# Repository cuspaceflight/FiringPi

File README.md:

# FiringPi

This project is designed to be run on a Raspberry Pi connected to various peripherals, to act as both fire controller
and datalogger for CUSF's White Dwarf hot and cold test fires. The utility files only run on linux, but you should be
able to work out equivalent commands for windows if you need to (if you do this please do put them in a .bat file and
pull request.).

## Requirements

To build on your local machine, you will need a native cross-compiler such
as [gcc/g++](https://www.gnu.org/software/gcc/) (You can change the compiler by editing the variable `$(GXX)` in a local
copy of the makfile and specifying `-f <local.makefile>` in the make command. The project
uses [ncurses](https://invisible-island.net/ncurses/announce.html) for its TUI, which works over standard ssh tty. You
will therefore need to make sure you have at least `libncurses5-dev` and `libncursesw5-dev` installed. When running on
the Raspberry Pi, [WiringPi](http://wiringpi.com/) is used for gpio access, which will need to be installed on your
local machine to compile if you wish to do so. The raspberry Pi also uses [tmux](https://linuxhandbook.com/tmux/) to
manage disconnects safely (the system leaving all of the valves open after an unhandled disconnect would not be good),
so if you use the script [/pi](/pi), then you will also require this. All of these are already installed on the flight
computer.

## Building and running

Clone the repo, then assert the directory is set up correctly with `make clean`. For a local build, use the makefile:

```console
make && ./main
```

To build on the Pi, you need to have ssh access, and make sure you have updated its IP address in either [/pi](/pi).
This file contains a script to upload source code directly to the Pi (with scp, no need for a git sync) and execute it
over ssh, forcing interactive terminal allocation, then building the project on the pi and executing it in a detatched
tmux session. You can also just run the executable on the pi in tmux without building with `./pi -r` or conversely to
build without running `./pi -b`

## Using the Program {curly brackets mean TODO}

Once you have launched the TUI successfully, you must launch the system into SAFE mode by pressing s[afe]. The system
may be armed by pressing <CTRL-A>, then {once you are satisfied that the system has booted correctly,} IGNITION mode may
be entered by pressing <SPACE>. The computer will then enter IGNITION, followed by FIRING and SHUTDOWN {as it runs the
preconfigured fire sequence}. An ABORT may be triggered by pressing <BACKSPACE> {or automatically by the system
detecting unsafe parameters}. ABORT mode can only be exitied by the computer, for safety reasons {currently press
e[rror] to debug exit}. SHUTDOWN exits to SAFE, and ABORT exits to ERROR, from which SAFE mode can be entered by
pressing s[afe]. To quit the program, the system must first be in the OFF state, entered by pressing o[ff] from SAFE
mode, only then it will exit when q[uit] is pressed.

## Project Structure

```markdown
cft-controller
├── build
│   ├── Display.o
│   ├── main.o
│   └── State.o
├── include
│   ├── Display.hpp
│   └── State.hpp
├── main
├── Makefile
├── pi
├── README.md
├── src
│   ├── Display.cpp
│   ├── main.cpp
│   └── State.cpp
└── TODO.md
```

## Useful Stuff

[ncurses HOWTO](https://tldp.org/HOWTO/NCURSES-Programming-HOWTO/)

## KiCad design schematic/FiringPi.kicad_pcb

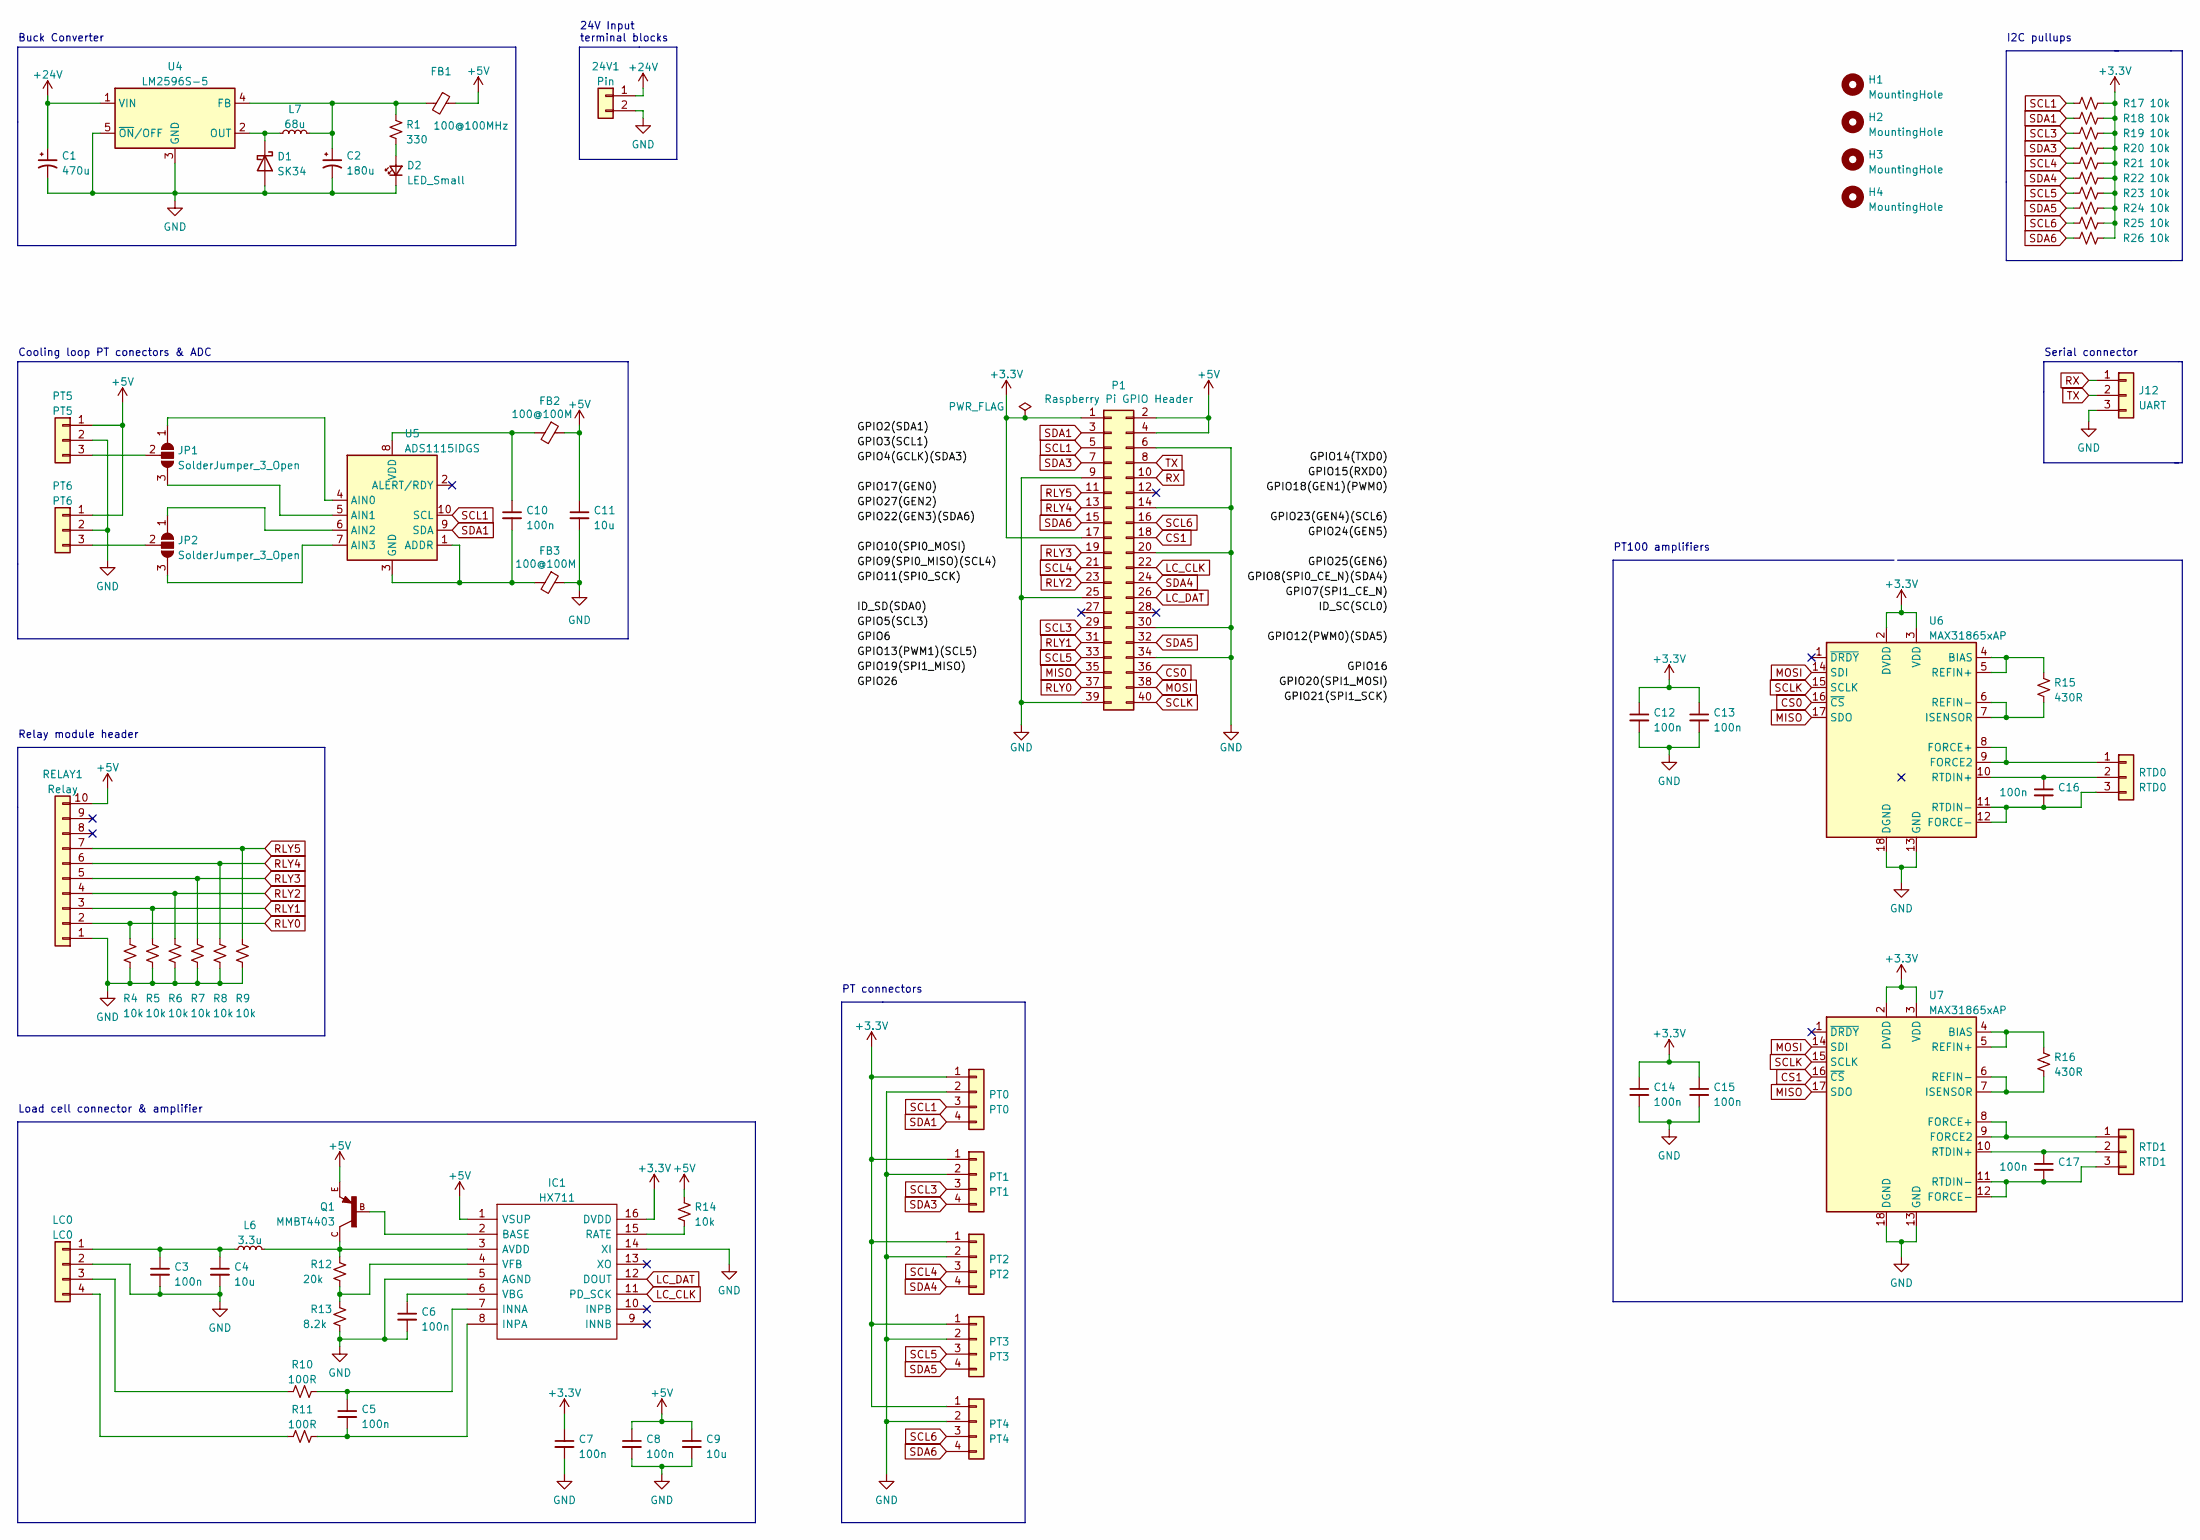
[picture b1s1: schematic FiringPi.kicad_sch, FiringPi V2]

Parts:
24V1: Pin; JST_XH_B2B-XH-A_1x02_P2.50mm_Vertical
C1: 470u; CP_Radial_D12.5mm_P5.00mm
C2: 180u; CP_Radial_D8.0mm_P3.50mm
C3, C5, C6, C7, C8, C10, C12, C13, C14, C15, C16, C17: 100n; C_0603_1608Metric
C4, C9, C11: 10u; C_0603_1608Metric
D1: SK34; D_SMC
D2: LED_Small; LED_0805_2012Metric
FB1: 100@100MHz; L_0805_2012Metric
FB2, FB3: 100@100M; L_0805_2012Metric
H1, H2, H3, H4: MountingHole; MountingHole_2.7mm_M2.5
IC1: HX711; SOIC127P600X160-16N; Manufacturer_Part_Number HX711
J12: UART; JST_XH_B3B-XH-A_1x03_P2.50mm_Vertical
JP1, JP2: SolderJumper_3_Open; SolderJumper-3_P1.3mm_Open_RoundedPad1.0x1.5mm
L6: 3.3u; L_0603_1608Metric
L7: 68u; PE-54038SNL
LC0: LC0; JST_XH_B4B-XH-A_1x04_P2.50mm_Vertical
P1: Raspberry Pi GPIO Header; PinSocket_2x20_P2.54mm_Vertical
PT0: PT0; JST_XH_B4B-XH-A_1x04_P2.50mm_Vertical
PT1: PT1; JST_XH_B4B-XH-A_1x04_P2.50mm_Vertical
PT2: PT2; JST_XH_B4B-XH-A_1x04_P2.50mm_Vertical
PT3: PT3; JST_XH_B4B-XH-A_1x04_P2.50mm_Vertical
PT4: PT4; JST_XH_B4B-XH-A_1x04_P2.50mm_Vertical
PT5: PT5; JST_XH_B3B-XH-A_1x03_P2.50mm_Vertical
PT6: PT6; JST_XH_B3B-XH-A_1x03_P2.50mm_Vertical
Q1: MMBT4403; SOT23-BEC
R1: 330; R_0603_1608Metric
R4, R5, R6, R7, R8, R9, R14, R17, R18, R19, R20, R21, R22, R23, R24, R25, R26: 10k; R_0603_1608Metric
R10, R11: 100R; R_0603_1608Metric
R12: 20k; R_0603_1608Metric
R13: 8.2k; R_0603_1608Metric
R15, R16: 430R; R_0603_1608Metric
RELAY1: Relay; PinHeader_1x10_P2.54mm_Vertical
RTD0: RTD0; JST_XH_B3B-XH-A_1x03_P2.50mm_Vertical
RTD1: RTD1; JST_XH_B3B-XH-A_1x03_P2.50mm_Vertical
U4: LM2596S-5; TO-263-5_TabPin3
U5: ADS1115IDGS; TSSOP-10_3x3mm_P0.5mm
U6, U7: MAX31865xAP; SSOP-20_5.3x7.2mm_P0.65mm

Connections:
+3.3V: C7.1, C12.1, C13.1, C14.1, C15.1, IC1.16 (DVDD), P1.1, P1.17, PT0.1, PT1.1, PT2.1, PT3.1, PT4.1, R17.1, R18.1, R19.1, R20.1, R21.1, R22.1, R23.1, R24.1, R25.1, R26.1, U6.2 (DVDD), U6.3 (VDD), U7.2 (DVDD), U7.3 (VDD)
+5V: C8.1, C9.1, C11.1, FB1.1, FB2.1, IC1.1 (VSUP), P1.2, P1.4, PT5.1, PT6.1, Q1.E, R14.1, RELAY1.10
+24V: 24V1.1, C1.1, U4.1 (VIN)
CS0: P1.36, U6.16 (~CS)
CS1: P1.18, U7.16 (~CS)
GND: 24V1.2, C1.2, C2.2, C3.2, C4.2, C6.2, C7.2, C8.2, C9.2, C11.2, C12.2, C13.2, C14.2, C15.2, D1.2 (A), D2.1 (K), FB3.1, IC1.5 (AGND), IC1.14 (XI), J12.3, LC0.2, P1.6, P1.9, P1.14, P1.20, P1.25, P1.30, P1.34, P1.39, PT0.2, PT1.2, PT2.2, PT3.2, PT4.2, PT5.2, PT6.2, R4.2, R5.2, R6.2, R7.2, R8.2, R9.2, R13.2, RELAY1.1, U4.3 (GND), U4.5 (~ON/OFF), U6.13 (GND), U6.18 (DGND), U6.19 (GND), U7.13 (GND), U7.18 (DGND), U7.19 (GND)
LC_CLK: IC1.11 (PD_SCK), P1.22
LC_DAT: IC1.12 (DOUT), P1.26
MISO: P1.35, U6.17 (SDO), U7.17 (SDO)
MOSI: P1.38, U6.14 (SDI), U7.14 (SDI)
unnamed: C2.1, FB1.2, L7.2, R1.1, U4.4 (FB)
unnamed: C3.1, C4.1, L6.1, LC0.1
unnamed: C5.1, IC1.7 (INNA), R10.1
unnamed: C5.2, IC1.8 (INPA), R11.1
unnamed: C6.1, IC1.6 (VBG)
unnamed: C10.1, FB2.2, U5.8 (VDD)
unnamed: C10.2, FB3.2, U5.1 (ADDR), U5.3 (GND)
unnamed: C16.1, RTD0.2, U6.10 (RTDIN+)
unnamed: C16.2, RTD0.3, U6.11 (RTDIN-), U6.12 (FORCE-)
unnamed: C17.1, RTD1.2, U7.10 (RTDIN+)
unnamed: C17.2, RTD1.3, U7.11 (RTDIN-), U7.12 (FORCE-)
unnamed: D1.1 (K), L7.1, U4.2 (OUT)
unnamed: D2.2 (A), R1.2
unnamed: IC1.2 (BASE), Q1.B
unnamed: IC1.3 (AVDD), L6.2, Q1.C, R12.1
unnamed: IC1.4 (VFB), R12.2, R13.1
unnamed: IC1.15 (RATE), R14.2
unnamed: JP1.1 (A), U5.4 (AIN0)
unnamed: JP1.2 (C), PT5.3
unnamed: JP1.3 (B), U5.5 (AIN1)
unnamed: JP2.1 (A), U5.6 (AIN2)
unnamed: JP2.2 (C), PT6.3
unnamed: JP2.3 (B), U5.7 (AIN3)
unnamed: LC0.3, R10.2
unnamed: LC0.4, R11.2
unnamed: R15.1, U6.4 (BIAS), U6.5 (REFIN+)
unnamed: R15.2, U6.6 (REFIN-), U6.7 (ISENSOR)
unnamed: R16.1, U7.4 (BIAS), U7.5 (REFIN+)
unnamed: R16.2, U7.6 (REFIN-), U7.7 (ISENSOR)
unnamed: RTD0.1, U6.8 (FORCE+), U6.9 (FORCE2)
unnamed: RTD1.1, U7.8 (FORCE+), U7.9 (FORCE2)
RLY0: P1.37, R4.1, RELAY1.2
RLY1: P1.31, R5.1, RELAY1.3
RLY2: P1.23, R6.1, RELAY1.4
RLY3: P1.19, R7.1, RELAY1.5
RLY4: P1.13, R8.1, RELAY1.6
RLY5: P1.11, R9.1, RELAY1.7
RX: J12.1, P1.10
SCL1: P1.5, PT0.3, R17.2, U5.10 (SCL)
SCL3: P1.29, PT1.3, R19.2
SCL4: P1.21, PT2.3, R21.2
SCL5: P1.33, PT3.3, R23.2
SCL6: P1.16, PT4.3, R25.2
SCLK: P1.40, U6.15 (SCLK), U7.15 (SCLK)
SDA1: P1.3, PT0.4, R18.2, U5.9 (SDA)
SDA3: P1.7, PT1.4, R20.2
SDA4: P1.24, PT2.4, R22.2
SDA5: P1.32, PT3.4, R24.2
SDA6: P1.15, PT4.4, R26.2
TX: J12.2, P1.8

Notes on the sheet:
Serial connector
PT100 amplifiers
PT connectors
I2C pullups
Load cell connector & amplifier
24V Input terminal blocks
Buck Converter
Relay module header
Cooling loop PT conectors & ADC

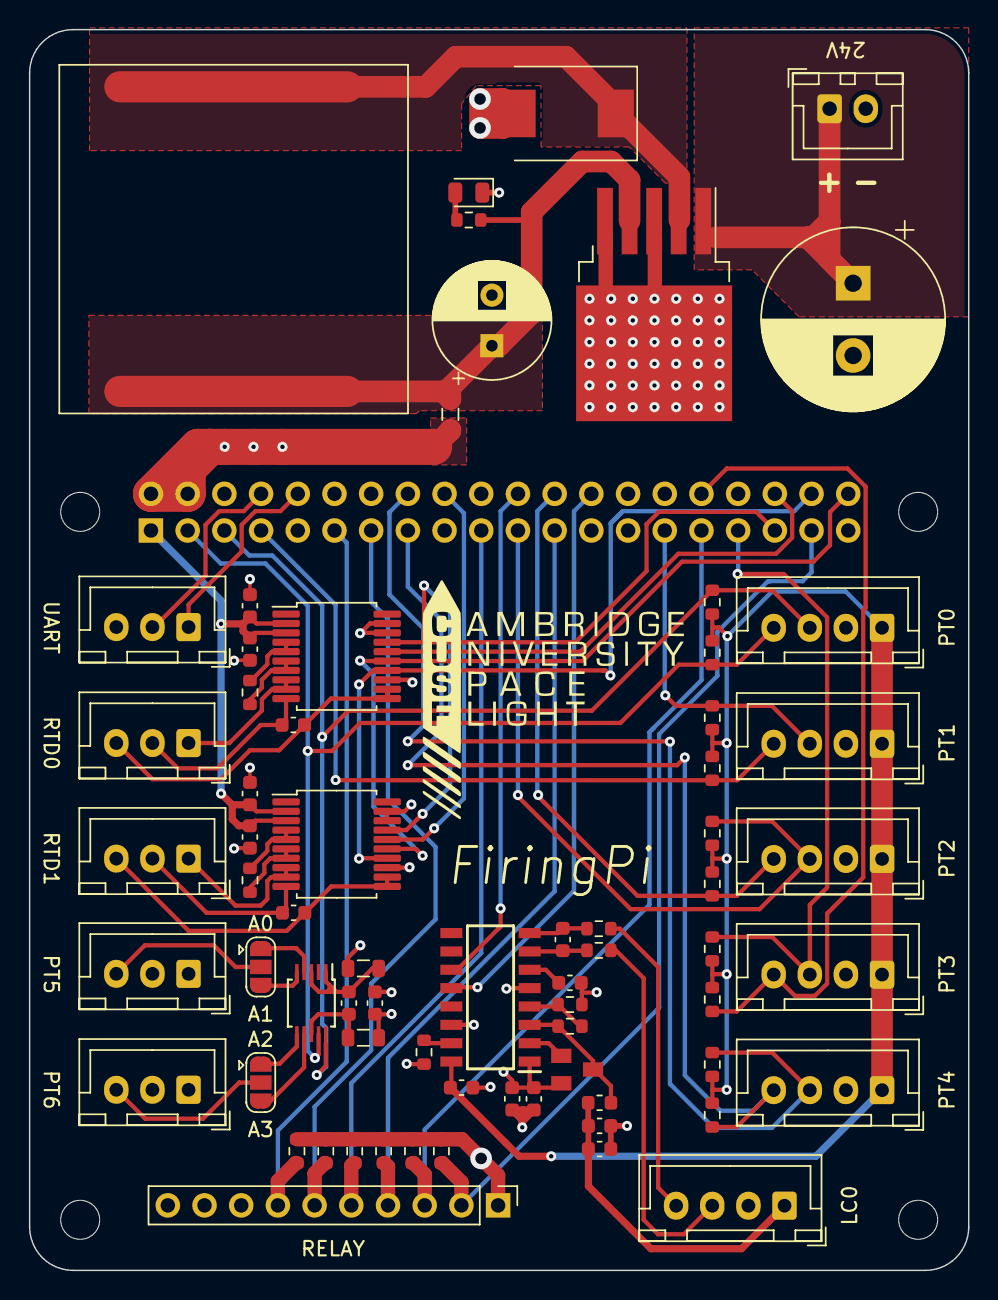
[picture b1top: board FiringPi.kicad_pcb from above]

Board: 4 copper layers, 65.0 x 85.9 mm, 74 parts (1 on the bottom side), 60 nets.

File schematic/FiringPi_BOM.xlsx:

FiringPi
Id | Designator | Package | Quantity | Designation | Part No | Suppplier | Supplier part no | Order quantity | Unit cost | Total cost
5 | J12 | JST_XH_B3B-XH-A_1x03_P2.50mm_Vertical | 5 | UART, PT5, PT6, RTD, RTD1 |  |  |  |  |  | 0
7 | PT0 | JST_XH_B4B-XH-A_1x04_P2.50mm_Vertical | 6 | PT0, PT1, PT2, PT3, PT4, LC0 |  |  |  |  |  | 0
24 | 24V1 | JST_XH_B2B-XH-A_1x02_P2.50mm_Vertical | 1 | Pin |  |  |  |  |  | 0
1 | C1 | CP_Radial_D12.5mm_P5.00mm | 1 | 470u | UPM1H471MHD | Mouser | 647-UPM1H471MHD6TN | 1 | 1.35 | 1.35
37 | C2 | CP_Radial_D8.0mm_P3.50mm | 1 | 180u | UPM1V181MPD | Mouser | 647-UPM1V181MPD | 1 | 0.739 | 0.739
2 | R22,R20,R17,R9,R24,R18,R23,R26,R5,R21,R19,R8,R7,R25,R4,R14,R6 | R_0603_1608Metric | 17 | 10k | RT0603FRE1310KL | Mouser | 603-RT0603FRE1310KL | 20 | 0.08799999999999999 | 1.76
4 | C16,C10,C5,C13,C6,C14,C3,C8,C12,C7,C15,C17 | C_0603_1608Metric | 12 | 100n | 06035C104JAT4A | Mouser | 581-06035C104JAT4A | 20 | 0.028 | 0.5600000000000001
6 | FB1,FB2,FB3 | L_0805_2012Metric | 3 | 100@100M | MFBM1V2012-101-R | Mouser | 704-MFBM1V2012-101-R | 10 | 0.027 | 0.27
9 | C4,C9,C11 | C_0603_1608Metric | 3 | 10u | 0603YD106KAT2A | Mouser | 581-0603YD106KAT2A | 4 | 0.572 | 2.288
10 | R10,R11 | R_0603_1608Metric | 2 | 100R | RC0603JR-07100RL | Mouser | 603-RC0603JR-07100RL | 10 | 0.016 | 0.16
11 | D2 | LED_0805_2012Metric | 1 | LED_Small | 150080VS75000 | Mouser | 710-150080VS75000 | 2 | 0.167 | 0.334
14 | U6,U7 | SSOP-20_5.3x7.2mm_P0.65mm | 2 | MAX31865xAP | MAX31865AAP+ | Mouser | 700-MAX31865AAP+ | 2 | 7.05 | 14.1
15 | R16,R15 | R_0603_1608Metric | 2 | 430R | NPW0603430RBEEA | Mouser | 71-TNPW0603430RBEEA | 3 | 0.59 | 1.77
16 | Q1 | SOT23-BEC | 1 | MMBT4403 | MMBT4403 | Mouser | 637-MMBT4403 | 2 | 0.361 | 0.722
18 | R13 | R_0603_1608Metric | 1 | 8.2k | RE0603FRE078K2L | Mouser | 603-RE0603FRE078K2L | 2 | 0.08799999999999999 | 0.176
20 | D1 | D_SMC | 1 | SK34 | SK34 | Mouser | 637-SK34 | 1 | 0.994 | 0.994
21 | L7 | PE-54038SNL | 1 | 68u | PE-54038SNLT | Mouer | 673-PE-54038SNLT | 1 | 3.19 | 3.19
22 | IC1 | SOIC127P600X160-16N | 1 | HX711 |  |  |  |  |  | 0
23 | R12 | R_0603_1608Metric | 1 | 20k | RC0603FR-1020KL | Mouser | 603-RC0603FR-1020KL | 2 | 0.08799999999999999 | 0.176
26 | R1 | R_0603_1608Metric | 1 | 330 | RC0603JR-07330RL | Mouser | 603-RC0603JR-07330RL | 10 | 0.013 | 0.13
27 | U5 | TSSOP-10_3x3mm_P0.5mm | 1 | ADS1115IDGS |  |  |  |  |  | 0
30 | RELAY1 | PinHeader_1x10_P2.54mm_Vertical | 1 | Relay |  |  |  |  |  | 0
35 | U4 | TO-263-5_TabPin3 | 1 | LM2596S-5 | LM2596SX-5.0/NOPB | Mouser | 926-LM2596SX-5.0NOPB | 1 | 6.04 | 6.04
36 | L6 | L_0603_1608Metric | 1 | 3.3u | MLF1608A3R3J | Mouser | 810-MLF1608A3R3J | 2 | 0.185 | 0.37
38 | P1 | PinSocket_2x20_P2.54mm_Vertical | 1 | Raspberry Pi GPIO Header |  |  |  |  |  | 0

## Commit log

2022-02-09 Basic ncurses interface setup and c++ skeleton/makefile
2022-02-09 fixing .gitignore and removing binaries
2022-02-10 added file to rsync source code to pi, compile then run it
2022-02-10 pretty colours
2022-02-11 more state transitions, plus some README
2022-02-11 Added windows support for code upload script: pi.bat
2022-02-11 added tmux script to handle disconnects, removed color checking for terminal as it works in mine and at the moment no one else has access to the Pi
2022-02-11 fix some merge issues
2022-02-12 changed rsync syntax to avoid copying non-updated files, like a makefile
2022-02-12 updated scipt for build and execution on pi
2022-02-13 instructions added to /pi
2022-02-13 refactor state machine into separate file
2022-02-14 syntax changes in pi and makefile
2022-02-14 finish switch to new dir names
2022-02-14 refactor further and add rough fps stabilization to reduce data rate over ssh
2022-02-21 Added TODO list
2022-02-22 yucky socket prototype, having issues getting the address to resolve for incoming connections but its definitely just me
2022-02-22 actually add the files
2022-02-22 makefile fix
2022-02-22 Rename makefile to Makefile and make includes more robust (because Andrew uses arch and arch has is *unique*)
2022-02-23 no changes
2022-02-23 change windows rm command in Makefile
2022-02-23 remove all traces of the sockets
2022-02-24 moving ncurses stuff into Display class - WIP
2022-02-24 finished Display port to separate class file, passing the pointer to the StateMachine class instance as a constructor argument which the Display class then keeps a reference to.
2022-02-24 update README.md and TODO.md, test ./pi still runs (it does, for the record)
2022-02-24 add Relay class
2022-02-25 add functionality and dummy code to state machine and Relay classes to support setting relay banks into state-driven configurations.
2022-02-25 Create LICENSE
2022-02-25 integrate valve patterns into StateMachine class
2022-03-09 rename to FiringPi
2022-03-09 some functions made static
2022-03-11 changed legacy pi script
2022-03-25 various changes, added PT class
2022-03-28 optimized PT class, changed access functionality to be ready for either threading or interrupt based data aquisition
2022-03-28 added functionality for adding more than one PT, handled exits by closing threads used for PT data acquisition, obeyed clang-tidy like a strict parent
2022-04-01 Graphing capability Added graphing for temp/pressure using unicode braille characters 0x2800 + (0->256). Capture rate currently locked to framerate (60Hz).
2022-04-24 2 PTs. Appears to work, but one PT is not functioning correctly so will need to test further
2022-04-25 Fix typos
2022-05-07 Add load cell readouts
2022-05-09 Added datalogger class
2022-05-12 Add initial logging functionality
2022-05-12 Add hdf5 libpath to makefile
2022-05-12 switched to c++ header
2022-05-12 Added basic csv logging
2022-05-13 Log P1 in hdf5
2022-05-23 add schematic
2022-05-26 ignore hdf5 files
2022-05-26 Add init state
2022-05-26 Update display diring startup to show init state
2022-05-26 Added load cell check on startup
2022-06-02 IMPORTANT Had to shorten the filename for output files so folder is now called "out" due to linux c++ crying
2022-06-02 small changes i forgot
2022-06-02 more small changes i forgot
2022-06-03 refactoring PT
2022-06-04 C++14 Smart Pointer Refactoring I have been led to believe that since 2014 this is how you use pointers in c++. Sorry for writing C-style c++ and sorry for this also probably being wrong
2022-06-05 ADC output Added template ADC output to the Display class. Compiles and runs fine, no way to test i2c until the hardware is fixed up.
2022-06-07 Fixed dumb mistakes If we read from the ADCs using i2cdump, works fine, but if we read using the c++ code, it causes the i2c to switch onto software mode for some reason.
2022-06-09 Add servo class
2022-06-09 Added 3rd servo
2022-06-09 Added servos to state machine
2022-06-13 Changed stuff over onto buses 1,3,4 because they seem to be the only ones working
2022-06-13 made graph iterate properly
2022-06-13 started graph scaling
2022-06-13 Graphs may now have customminputs and scale appropriately
2022-06-14 Graphs and a little work on load cells and ADCs
2022-06-16 Small changes to pins etc.
2022-06-16 Changes without access to the pi to check. - Added log outputs for all data channels except the ADCs. - Allowed the StateMachine valve matrix to set servo values - Added all 3 load cells
2022-06-17 More untested changes - ability to select different data screens in the Display class
2022-06-17 - Added labels to graphs - Added rest of data outputs to be plotted at top of screen
2022-06-17 Added manual mode accessible via CTRL-M. [0] toggles the helium servo and [1-6] toggles the solenoid relays
2022-06-17 pre-test day
2022-06-18 test day begin
2022-07-26 ## week before hot fire - UI changes - corrected ordering of PTs - added readout for relay channel outputs
2022-08-01 Day before Hot Fire **untested** - all changes made are commented as such, **must uncomment!** - added auto-tare to the loadcell during init (240 samples ~3s) - LoadCell.get_weight() now returns adju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
2022-08-01 Add readReg
2022-08-01 loadcell kept manual, noted down refUnit if we want it in that format.
    Going to bed. Sleep is important
2022-12-24 Schamatic changes
2022-12-29 Updated schematic
2023-01-27 Added V2 Pi hat style PCB
2023-01-27 Updated silkscreen labels
2023-01-29 Fixed DRC errors
2023-01-29 Small tweaks
2023-01-29 Added BOM & part Nos
2023-01-29 Generated gerbers
2023-02-19 Added BOM with Farnell part nos
2023-06-26 Added ADS1115 driver
2023-06-29 RTD test program
2023-07-01 Relays working
2023-07-01 i2c PTs working
2023-07-01 ADC not working
2023-07-01 ADC not working 2
2023-07-01 ADC not working 3

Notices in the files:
parts and their libraries:
Copyright 2021 Accelerated Designs. All rights reserved.
